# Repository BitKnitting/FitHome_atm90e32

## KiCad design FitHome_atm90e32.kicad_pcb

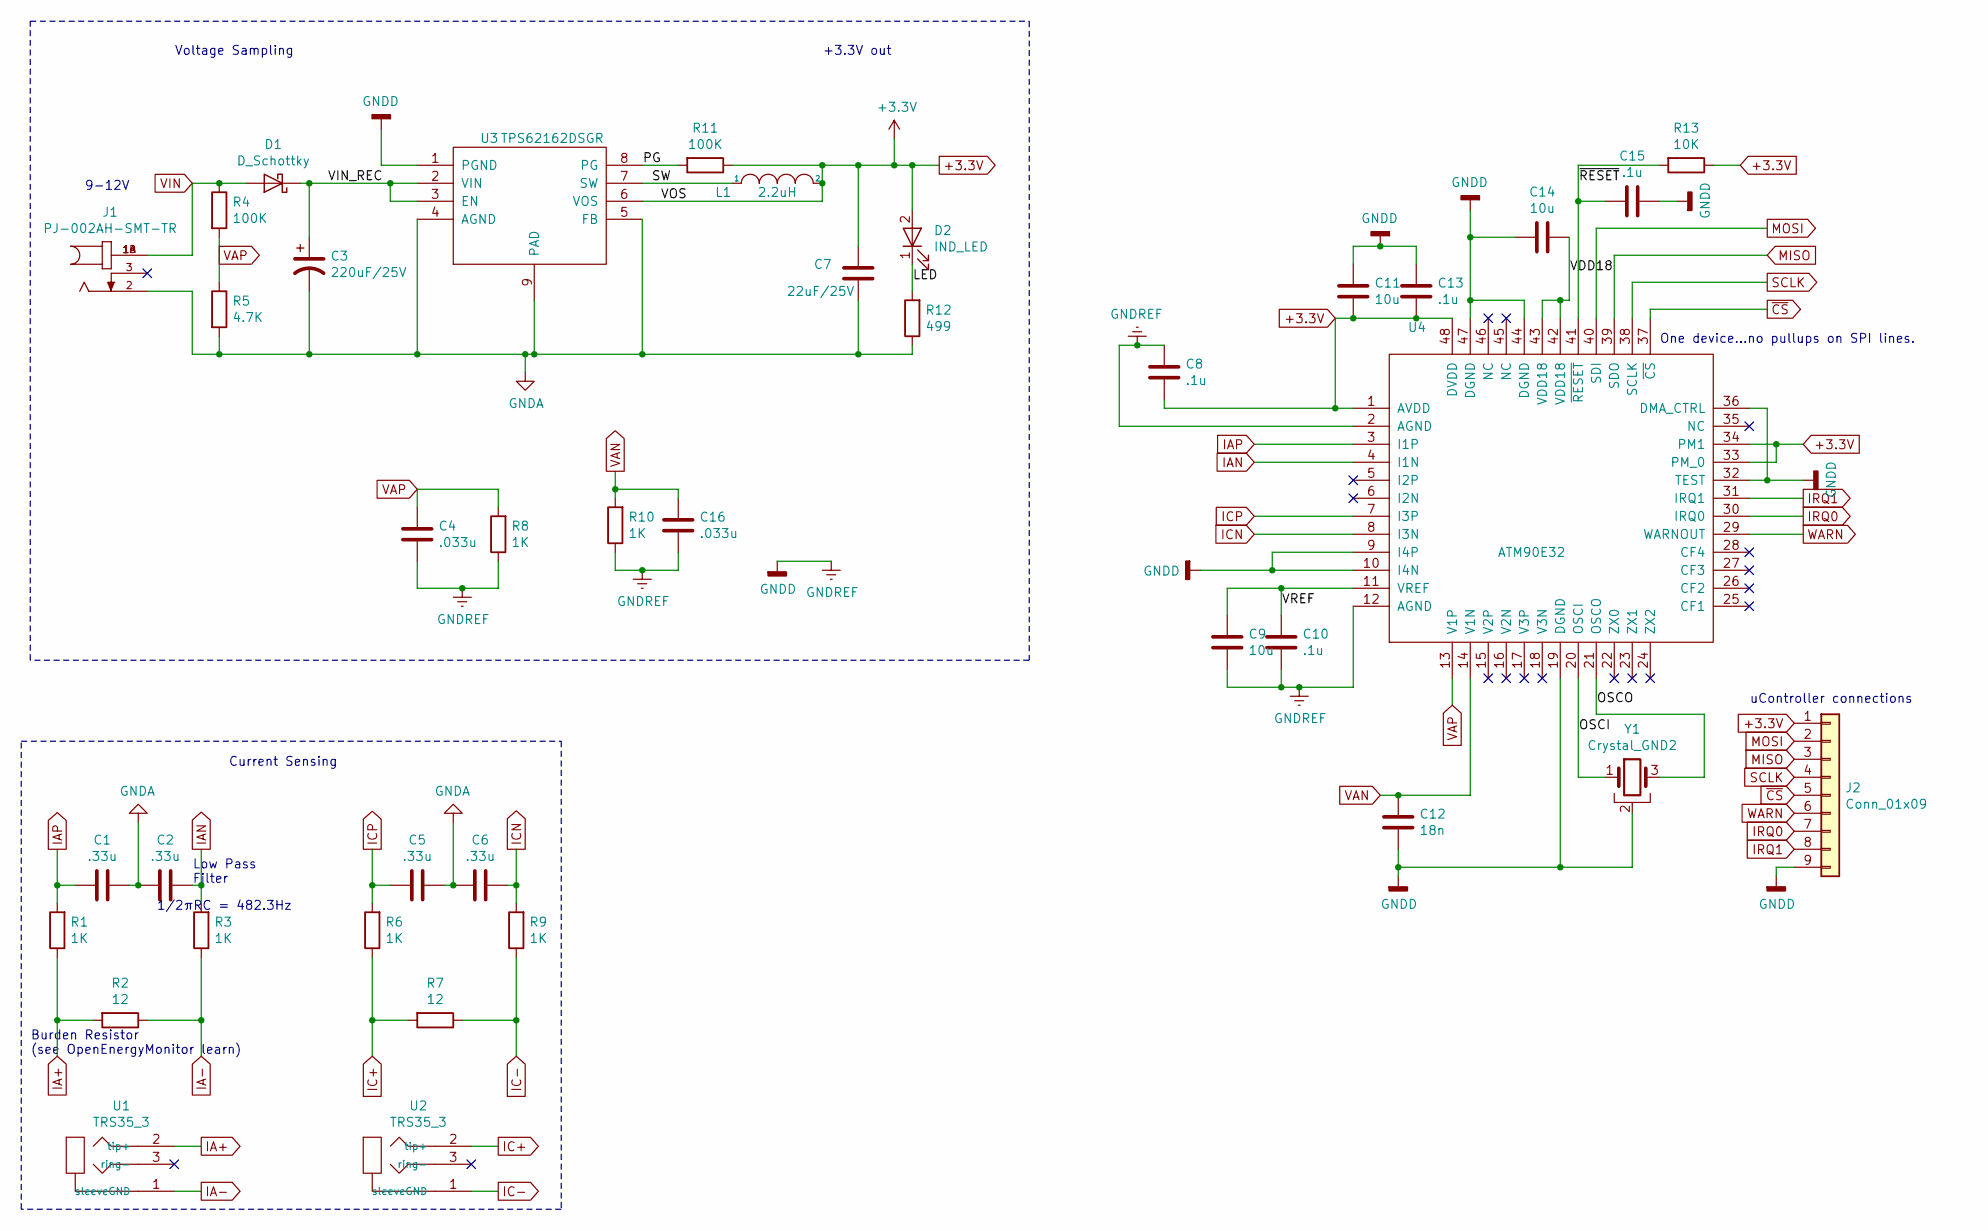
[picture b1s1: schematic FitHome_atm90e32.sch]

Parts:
C1, C2, C5, C6: .33u; C_0805_2012Metric
C3: 220uF/25V; UCW1V100MCL1GS
C4, C16: .033u; C_0805_2012Metric
C7: 22uF/25V; C_0805_2012Metric
C8, C10, C13, C15: .1u; C_0805_2012Metric
C9, C11, C14: 10u; C_0805_2012Metric
C12: 18n; C_0805_2012Metric
D1: D_Schottky; FM5819-W
D2: IND_LED; D_0805_2012Metric
J1: PJ-002AH-SMT-TR; CUI_PJ-002AH-SMT-TR
J2: Conn_01x09; 9Pin-bb
L1: 2.2uH; PA4332.XXXNLT
R1, R3, R6, R8, R9, R10: 1K; R_0805_2012Metric
R2, R7: 12; R_0805_2012Metric
R4, R11: 100K; R_0805_2012Metric
R5: 4.7K; R_0805_2012Metric
R12: 499; R_0805_2012Metric
R13: 10K; R_0805_2012Metric
U1, U2: TRS35_3; Audio-Jack
U3: TPS62162DSGR
U4: ATM90E32; QFP50P900X900X120-48N
Y1: Crystal_GND2; XTAL_FA-238_25.0000MB-C3

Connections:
+3.3V: C7.1, C8.2, C11.2, C13.2, D2.2 (A), J2.1, L1.2, R11.1, R13.1, U3.6 (VOS), U4.1 (AVDD), U4.33 (PM_0), U4.34 (PM1), U4.48 (DVDD)
/LED: D2.1 (K), R12.2
/OSCI: U4.20 (OSCI), Y1.1
/OSCO: U4.21 (OSCO), Y1.3
/PG: R11.2, U3.8 (PG)
/SW: L1.1, U3.7 (SW)
/VDD18: C14.1, U4.42 (VDD18), U4.43 (VDD18)
/VIN_REC: C3.1, D1.1 (K), U3.2 (VIN), U3.3 (EN)
/VREF: C9.1, C10.1, U4.11 (VREF)
/~RESET: C15.2, R13.2, U4.41 (~RESET)
GNDA: C1.1, C2.2, C3.2, C5.1, C6.2, C7.2, J1.2, R5.2, R12.1, U3.4 (AGND), U3.5 (FB), U3.9 (PAD)
GNDD: C4.1, C8.1, C9.2, C10.2, C11.1, C12.2, C13.1, C14.2, C15.1, C16.1, J2.9, R8.1, R10.1, U3.1 (PGND), U4.2 (AGND), U4.9 (I4P), U4.10 (I4N), U4.12 (AGND), U4.19 (DGND), U4.32 (TEST), U4.36 (DMA_CTRL), U4.44 (DGND), U4.47 (DGND), Y1.2
IA+: R1.1, R2.2, U1.2 (tip+)
IA-: R2.1, R3.1, U1.1 (sleeveGND)
IAN: C2.1, R3.2, U4.4 (I1N)
IAP: C1.2, R1.2, U4.3 (I1P)
IC+: R6.1, R7.2, U2.2 (tip+)
IC-: R7.1, R9.1, U2.1 (sleeveGND)
ICN: C6.1, R9.2, U4.8 (I3N)
ICP: C5.2, R6.2, U4.7 (I3P)
IRQ0: J2.7, U4.30 (IRQ0)
IRQ1: J2.8, U4.31 (IRQ1)
MISO: J2.3, U4.39 (SDO)
MOSI: J2.2, U4.40 (SDI)
SCLK: J2.4, U4.38 (SCLK)
VAN: C12.1, C16.2, R10.2, U4.14 (V1N)
VAP: C4.2, R4.2, R5.1, R8.2, U4.13 (V1P)
VIN: D1.2 (A), J1.1A (1), J1.1B (1), R4.1
WARN: J2.6, U4.29 (WARNOUT)
~CS: J2.5, U4.37 (~CS)

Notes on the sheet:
Current Sensing
Burden Resistor (see OpenEnergyMonitor learn)
Low Pass Filter
9-12V
1/2πRC = 482.3Hz
One device…no pullups on SPI lines.
Voltage Sampling
+3.3V out
uController connections

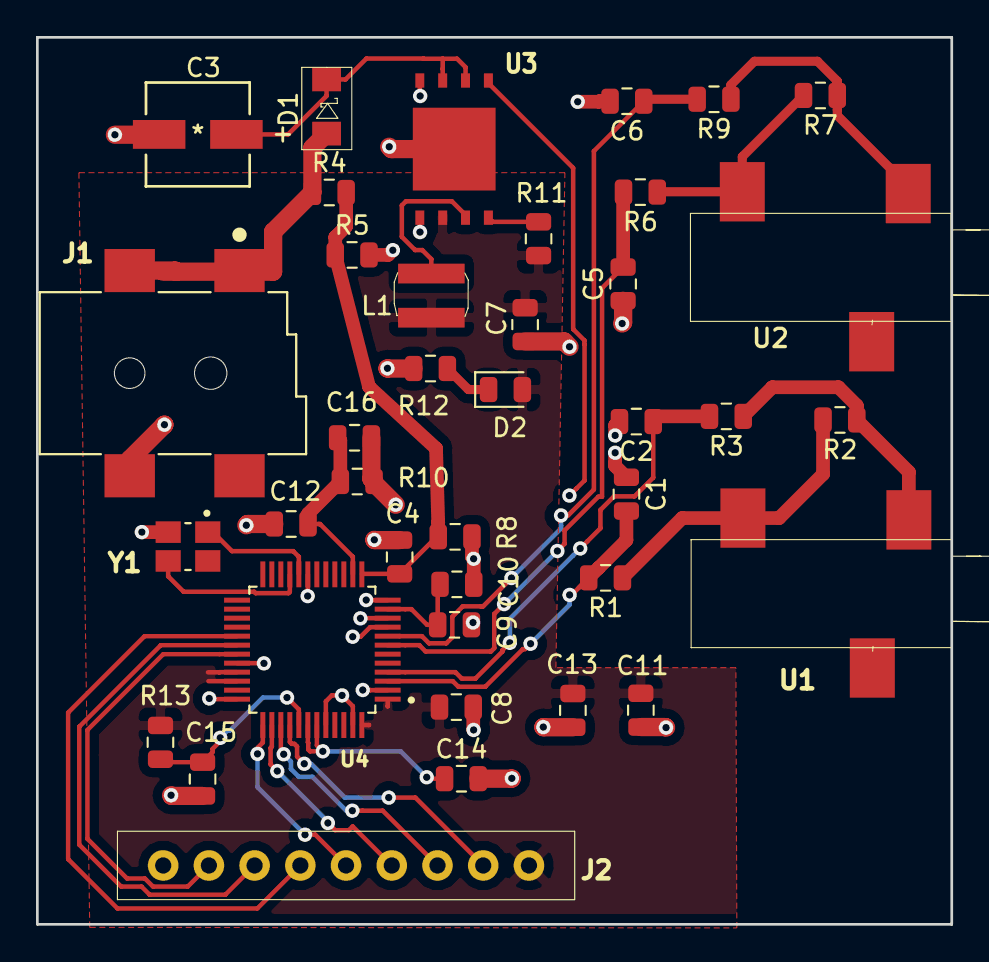
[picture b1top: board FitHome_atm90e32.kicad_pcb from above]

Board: 2 copper layers, 50.8 x 49.3 mm, 39 parts (0 on the bottom side), 30 nets.

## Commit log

2019-05-21 OSH Park - first build

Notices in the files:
parts and their libraries:
Copyright 2016 Accelerated Designs. All rights reserved.
